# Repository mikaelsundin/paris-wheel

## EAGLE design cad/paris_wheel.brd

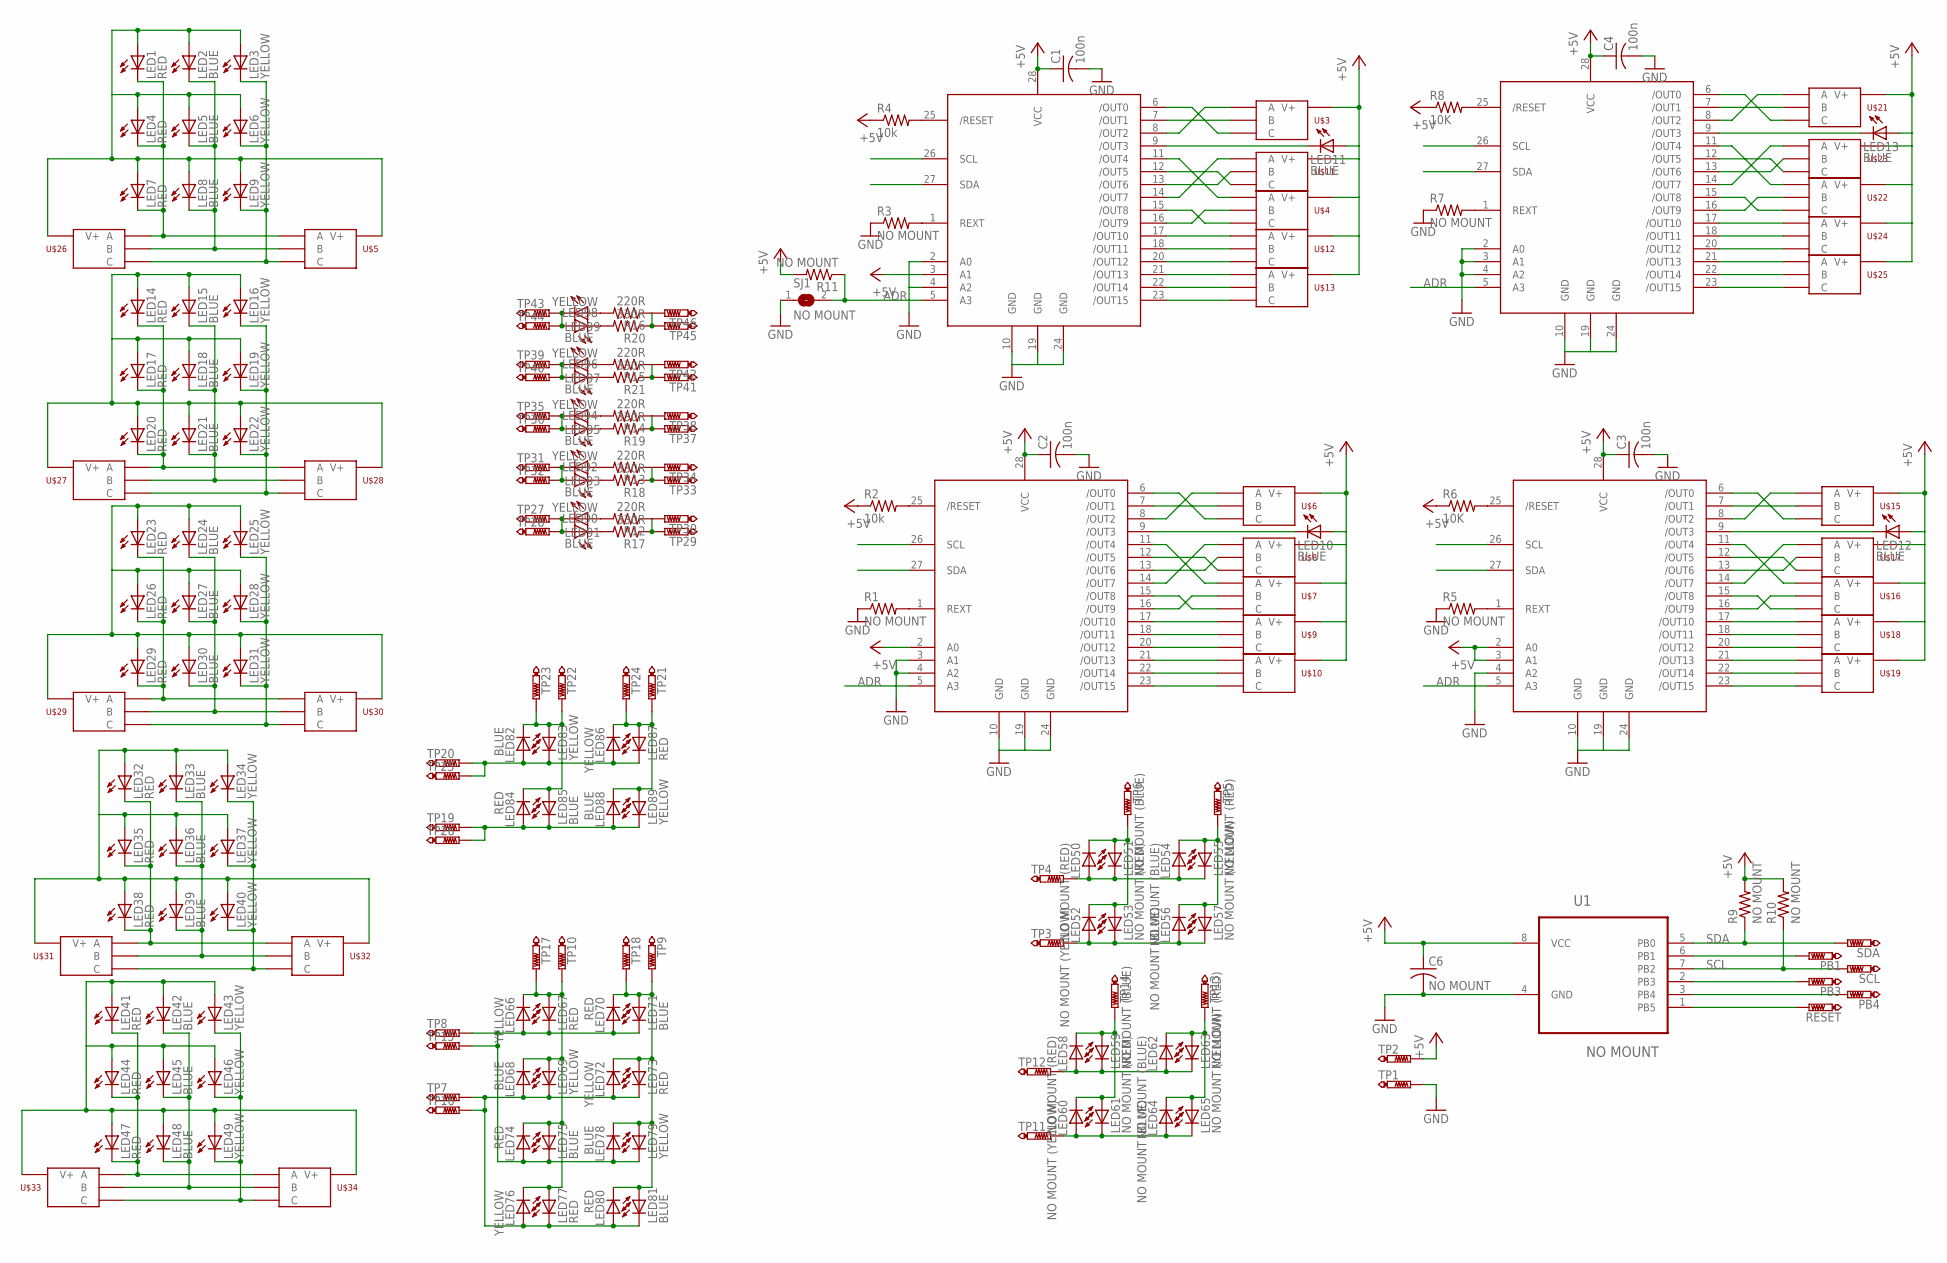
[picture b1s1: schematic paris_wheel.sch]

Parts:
C1, C2, C3, C4: 100n; C0603
C6: NO MOUNT; C0603
LED1, LED4, LED7, LED14, LED17, LED20, LED23, LED26, LED29, LED32, LED35, LED38, LED41, LED44, LED47, LED67, LED70, LED73, LED74, LED77, LED80, LED84, LED87: RED; CHIP-LED0603
LED2, LED5, LED8, LED10, LED11, LED12, LED13, LED15, LED18, LED21, LED24, LED27, LED30, LED33, LED36, LED39, LED42, LED45, LED48, LED68, LED71, LED75, LED78, LED81, LED82, LED85, LED88, LED91, LED93, LED95, LED97, LED99: BLUE; CHIP-LED0603
LED3, LED6, LED9, LED16, LED19, LED22, LED25, LED28, LED31, LED34, LED37, LED40, LED43, LED46, LED49, LED66, LED69, LED72, LED76, LED79, LED83, LED86, LED89, LED90, LED92, LED94, LED96, LED98: YELLOW; CHIP-LED0603
LED50, LED53, LED55, LED58, LED61, LED63: NO MOUNT (RED); CHIP-LED0603
LED51, LED54, LED56, LED59, LED62, LED64: NO MOUNT (BLUE); CHIP-LED0603
LED52, LED57, LED60, LED65: NO MOUNT (YELLOW); CHIP-LED0603
PB1, PB3, PB4: TESTPAD; TP20SQ
R1, R3, R5, R7, R9, R10, R11: NO MOUNT; R0603
R2, R4: 10k; R0603
R6, R8: 10K; R0603
R12, R13, R14, R15, R16: 220R; R0603
R17, R18, R19, R20, R21: 330R; R0603
RESET: TESTPAD; TP20SQ
SCL: TESTPAD; TP20SQ
SDA: TESTPAD; TP20SQ
SJ1: NO MOUNT; SJ
TP1, TP2: TESTPAD; TP20SQ
TP3, TP4, TP5, TP6, TP7, TP8, TP9, TP10, TP11, TP12, TP13, TP14, TP15, TP16, TP17, TP18, TP19, TP20, TP21, TP22, TP23, TP24, TP25, TP26, TP27, TP28, TP29, TP30, TP31, TP32, TP33, TP34, TP35, TP36, TP37, TP38, TP39, TP40, TP41, TP42, TP43, TP44, TP45, TP46: TESTPAD; TP15SQ
U1: NO MOUNT; SOIC127P798X216-8N
U$1, U$2, U$14, U$20: TLC59116IPWR; TSSOP28
U$3, U$4, U$5, U$6, U$7, U$8, U$9, U$10, U$11, U$12, U$13, U$15, U$16, U$17, U$18, U$19, U$21, U$22, U$23, U$24, U$25, U$26, U$27, U$28, U$29, U$30, U$31, U$32, U$33, U$34: NO MOUNT; MINI-PCB-CONNECTOR

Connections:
+5V: C1.1, C2.1, C3.1, C4.1, C6.1, LED10.A, LED11.A, LED12.A, LED13.A, R2.1, R4.1, R6.1, R8.1, R9.2, R10.2, R11.2, TP2.TP, U1.8 (VCC), U$1.2 (A0), U$1.28 (VCC), U$2.3 (A1), U$2.28 (VCC), U$3.A (V+), U$4.A (V+), U$6.A (V+), U$7.A (V+), U$8.A (V+), U$9.A (V+), U$10.A (V+), U$11.A (V+), U$12.A (V+), U$13.A (V+), U$14.2 (A0), U$14.3 (A1), U$14.28 (VCC), U$15.A (V+), U$16.A (V+), U$17.A (V+), U$18.A (V+), U$19.A (V+), U$20.28 (VCC), U$21.A (V+), U$22.A (V+), U$23.A (V+), U$24.A (V+), U$25.A (V+)
ADR: R11.1, SJ1.2, U$1.5 (A3), U$2.5 (A3), U$14.5 (A3), U$20.5 (A3)
GND: C1.2, C2.2, C3.2, C4.2, C6.2, R1.1, R3.1, R5.1, R7.1, SJ1.1, TP1.TP, U1.4 (GND), U$1.3 (A1), U$1.4 (A2), U$1.10 (GND), U$1.19 (GND), U$1.24 (GND), U$2.2 (A0), U$2.4 (A2), U$2.10 (GND), U$2.19 (GND), U$2.24 (GND), U$14.4 (A2), U$14.10 (GND), U$14.19 (GND), U$14.24 (GND), U$20.2 (A0), U$20.3 (A1), U$20.4 (A2), U$20.10 (GND), U$20.19 (GND), U$20.24 (GND)
unnamed: R2.2, U$1.25 (/RESET)
unnamed: LED1.A, LED2.A, LED3.A, LED4.A, LED5.A, LED6.A, LED7.A, LED8.A, LED9.A, U$5.A (V+), U$26.B (V+)
unnamed: R3.2, U$2.1 (REXT)
unnamed: LED1.C, LED4.C, LED7.C, U$5.V+ (A), U$26.C (A)
unnamed: LED2.C, LED5.C, LED8.C, U$5.C (B), U$26.V+ (B)
unnamed: LED3.C, LED6.C, LED9.C, U$5.B (C), U$26.A (C)
unnamed: U$1.6 (/OUT0), U$6.B (C)
unnamed: R1.2, U$1.1 (REXT)
unnamed: U$2.7 (/OUT1), U$3.C (B)
unnamed: U$1.7 (/OUT1), U$6.C (B)
unnamed: U$1.8 (/OUT2), U$6.V+ (A)
unnamed: U$1.12 (/OUT5), U$8.B (C)
unnamed: U$1.13 (/OUT6), U$8.C (B)
unnamed: U$1.15 (/OUT8), U$7.B (C)
unnamed: U$1.16 (/OUT9), U$7.C (B)
unnamed: U$1.14 (/OUT7), U$8.V+ (A)
unnamed: U$1.11 (/OUT4), U$7.V+ (A)
unnamed: U$1.17 (/OUT10), U$9.V+ (A)
unnamed: U$1.18 (/OUT11), U$9.C (B)
unnamed: U$1.20 (/OUT12), U$9.B (C)
unnamed: U$1.21 (/OUT13), U$10.V+ (A)
unnamed: U$1.22 (/OUT14), U$10.C (B)
unnamed: U$1.23 (/OUT15), U$10.B (C)
unnamed: LED10.C, U$1.9 (/OUT3)
unnamed: U$2.17 (/OUT10), U$12.V+ (A)
unnamed: U$2.18 (/OUT11), U$12.C (B)
unnamed: U$2.20 (/OUT12), U$12.B (C)
unnamed: U$2.21 (/OUT13), U$13.V+ (A)
unnamed: U$2.22 (/OUT14), U$13.C (B)
unnamed: U$2.23 (/OUT15), U$13.B (C)
unnamed: U$2.13 (/OUT6), U$11.C (B)
unnamed: U$2.11 (/OUT4), U$4.V+ (A)
unnamed: LED11.C, U$2.9 (/OUT3)
unnamed: U$2.6 (/OUT0), U$3.B (C)
unnamed: U$2.8 (/OUT2), U$3.V+ (A)
unnamed: U$2.15 (/OUT8), U$4.B (C)
unnamed: U$2.16 (/OUT9), U$4.C (B)
unnamed: U$2.12 (/OUT5), U$11.B (C)
unnamed: U$2.14 (/OUT7), U$11.V+ (A)
unnamed: R4.2, U$2.25 (/RESET)
unnamed: R5.2, U$14.1 (REXT)
unnamed: U$14.7 (/OUT1), U$15.C (B)
unnamed: U$14.17 (/OUT10), U$18.V+ (A)
unnamed: U$14.18 (/OUT11), U$18.C (B)
unnamed: U$14.20 (/OUT12), U$18.B (C)
unnamed: U$14.21 (/OUT13), U$19.V+ (A)
unnamed: U$14.22 (/OUT14), U$19.C (B)
unnamed: U$14.23 (/OUT15), U$19.B (C)
unnamed: U$14.13 (/OUT6), U$17.C (B)
unnamed: U$14.11 (/OUT4), U$16.V+ (A)
unnamed: LED12.C, U$14.9 (/OUT3)
unnamed: U$14.6 (/OUT0), U$15.B (C)
unnamed: U$14.8 (/OUT2), U$15.V+ (A)
unnamed: U$14.15 (/OUT8), U$16.B (C)
unnamed: U$14.16 (/OUT9), U$16.C (B)
unnamed: U$14.12 (/OUT5), U$17.B (C)
unnamed: U$14.14 (/OUT7), U$17.V+ (A)
unnamed: R6.2, U$14.25 (/RESET)
unnamed: R7.2, U$20.1 (REXT)
unnamed: U$20.7 (/OUT1), U$21.C (B)
unnamed: U$20.17 (/OUT10), U$24.V+ (A)
unnamed: U$20.18 (/OUT11), U$24.C (B)
unnamed: U$20.20 (/OUT12), U$24.B (C)
unnamed: U$20.21 (/OUT13), U$25.V+ (A)
unnamed: U$20.22 (/OUT14), U$25.C (B)
unnamed: U$20.23 (/OUT15), U$25.B (C)
unnamed: U$20.13 (/OUT6), U$23.C (B)
unnamed: U$20.11 (/OUT4), U$22.V+ (A)
unnamed: LED13.C, U$20.9 (/OUT3)
unnamed: U$20.6 (/OUT0), U$21.B (C)
unnamed: U$20.8 (/OUT2), U$21.V+ (A)
unnamed: U$20.15 (/OUT8), U$22.B (C)
unnamed: U$20.16 (/OUT9), U$22.C (B)
unnamed: U$20.12 (/OUT5), U$23.B (C)
unnamed: U$20.14 (/OUT7), U$23.V+ (A)
unnamed: R8.2, U$20.25 (/RESET)
unnamed: RESET.TP, U1.1 (PB5)
unnamed: PB3.TP, U1.2 (PB3)
unnamed: PB4.TP, U1.3 (PB4)
unnamed: PB1.TP, U1.6 (PB1)
unnamed: LED14.A, LED15.A, LED16.A, LED17.A, LED18.A, LED19.A, LED20.A, LED21.A, LED22.A, U$27.B (V+), U$28.A (V+)
unnamed: LED14.C, LED17.C, LED20.C, U$27.C (A), U$28.V+ (A)
unnamed: LED15.C, LED18.C, LED21.C, U$27.V+ (B), U$28.C (B)
unnamed: LED16.C, LED19.C, LED22.C, U$27.A (C), U$28.B (C)
unnamed: LED23.A, LED24.A, LED25.A, LED26.A, LED27.A, LED28.A, LED29.A, LED30.A, LED31.A, U$29.B (V+), U$30.A (V+)
unnamed: LED23.C, LED26.C, LED29.C, U$29.C (A), U$30.V+ (A)
unnamed: LED24.C, LED27.C, LED30.C, U$29.V+ (B), U$30.C (B)
unnamed: LED25.C, LED28.C, LED31.C, U$29.A (C), U$30.B (C)
unnamed: LED32.A, LED33.A, LED34.A, LED35.A, LED36.A, LED37.A, LED38.A, LED39.A, LED40.A, U$31.B (V+), U$32.A (V+)
unnamed: LED32.C, LED35.C, LED38.C, U$31.C (A), U$32.V+ (A)
unnamed: LED33.C, LED36.C, LED39.C, U$31.V+ (B), U$32.C (B)
unnamed: LED34.C, LED37.C, LED40.C, U$31.A (C), U$32.B (C)
unnamed: LED41.A, LED42.A, LED43.A, LED44.A, LED45.A, LED46.A, LED47.A, LED48.A, LED49.A, U$33.B (V+), U$34.A (V+)
unnamed: LED41.C, LED44.C, LED47.C, U$33.C (A), U$34.V+ (A)
unnamed: LED42.C, LED45.C, LED48.C, U$33.V+ (B), U$34.C (B)
unnamed: LED43.C, LED46.C, LED49.C, U$33.A (C), U$34.B (C)
unnamed: LED50.A, LED51.C, LED54.A, LED55.C, TP4.TP
unnamed: LED54.C, LED55.A, LED56.C, LED57.A, TP5.TP
unnamed: LED50.C, LED51.A, LED52.C, LED53.A, TP6.TP
unnamed: LED52.A, LED53.C, LED56.A, LED57.C, TP3.TP
unnamed: LED58.A, LED59.C, LED62.A, LED63.C, TP12.TP
unnamed: LED58.C, LED59.A, LED60.C, LED61.A, TP14.TP
unnamed: LED60.A, LED61.C, LED64.A, LED65.C, TP11.TP
unnamed: LED62.C, LED63.A, LED64.C, LED65.A, TP13.TP
unnamed: LED82.A, LED83.C, LED86.A, LED87.C, TP20.TP, TP25.TP
unnamed: LED82.C, LED83.A, LED84.C, LED85.A, TP22.TP, TP23.TP
unnamed: LED84.A, LED85.C, LED88.A, LED89.C, TP19.TP, TP26.TP
unnamed: LED86.C, LED87.A, LED88.C, LED89.A, TP21.TP, TP24.TP
unnamed: LED66.A, LED67.C, LED70.A, LED71.C, LED74.A, LED75.C, LED78.A, LED79.C, TP8.TP, TP15.TP
unnamed: LED66.C, LED67.A, LED68.C, LED69.A, LED74.C, LED75.A, LED76.C, LED77.A, TP10.TP, TP17.TP
unnamed: LED68.A, LED69.C, LED72.A, LED73.C, LED76.A, LED77.C, LED80.A, LED81.C, TP7.TP, TP16.TP
unnamed: LED70.C, LED71.A, LED72.C, LED73.A, LED78.C, LED79.A, LED80.C, LED81.A, TP9.TP, TP18.TP
unnamed: R12.1, R17.1, TP29.TP, TP30.TP
unnamed: LED90.A, LED91.C, TP27.TP, TP28.TP
unnamed: LED91.A, R12.2
unnamed: LED92.A, LED93.C, TP31.TP, TP32.TP
unnamed: R13.1, R18.1, TP33.TP, TP34.TP
unnamed: LED93.A, R13.2
unnamed: LED94.A, LED95.C, TP35.TP, TP36.TP
unnamed: R14.1, R19.1, TP37.TP, TP38.TP
unnamed: LED95.A, R14.2
unnamed: LED96.A, LED97.C, TP39.TP, TP40.TP
unnamed: R15.1, R21.1, TP41.TP, TP42.TP
unnamed: LED97.A, R15.2
unnamed: LED98.A, LED99.C, TP43.TP, TP44.TP
unnamed: R16.1, R20.1, TP45.TP, TP46.TP
unnamed: LED99.A, R16.2
unnamed: LED90.C, R17.2
unnamed: LED92.C, R18.2
unnamed: LED94.C, R19.2
unnamed: LED98.C, R20.2
unnamed: LED96.C, R21.2
SCL: R10.1, SCL.TP, U1.7 (PB2), U$1.26 (SCL), U$2.26 (SCL), U$14.26 (SCL), U$20.26 (SCL)
SDA: R9.1, SDA.TP, U1.5 (PB0), U$1.27 (SDA), U$2.27 (SDA), U$14.27 (SDA), U$20.27 (SDA)

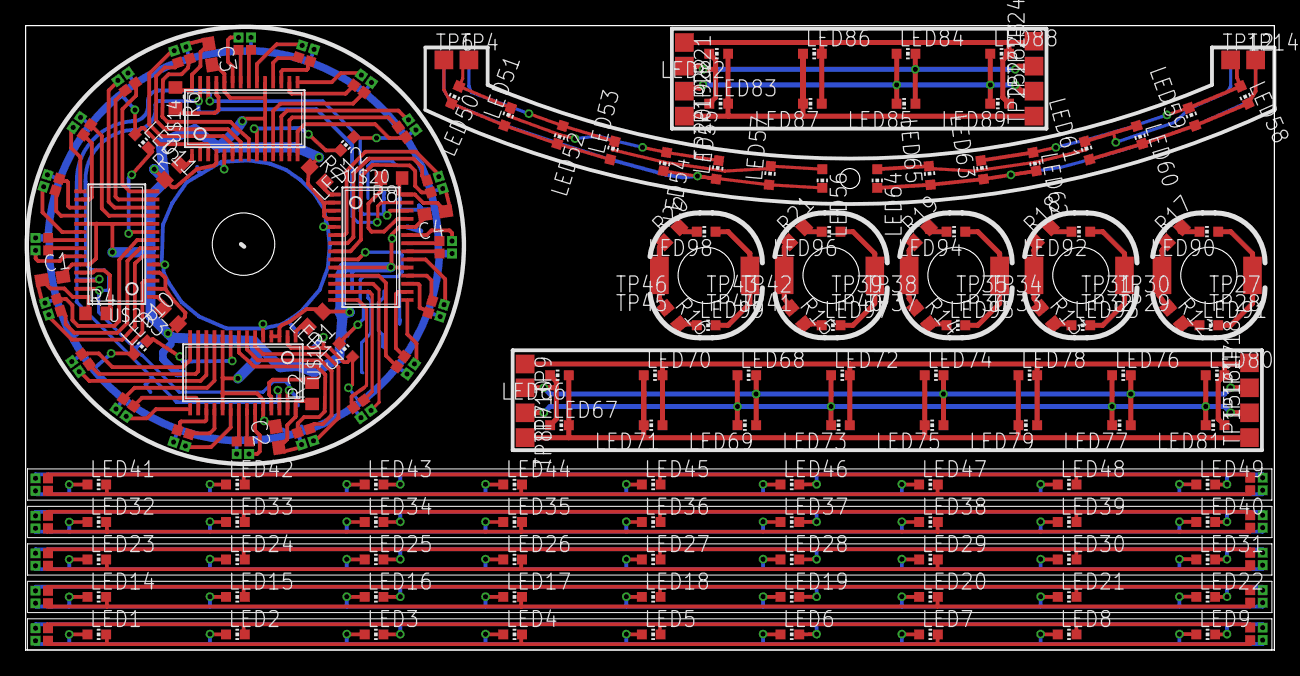
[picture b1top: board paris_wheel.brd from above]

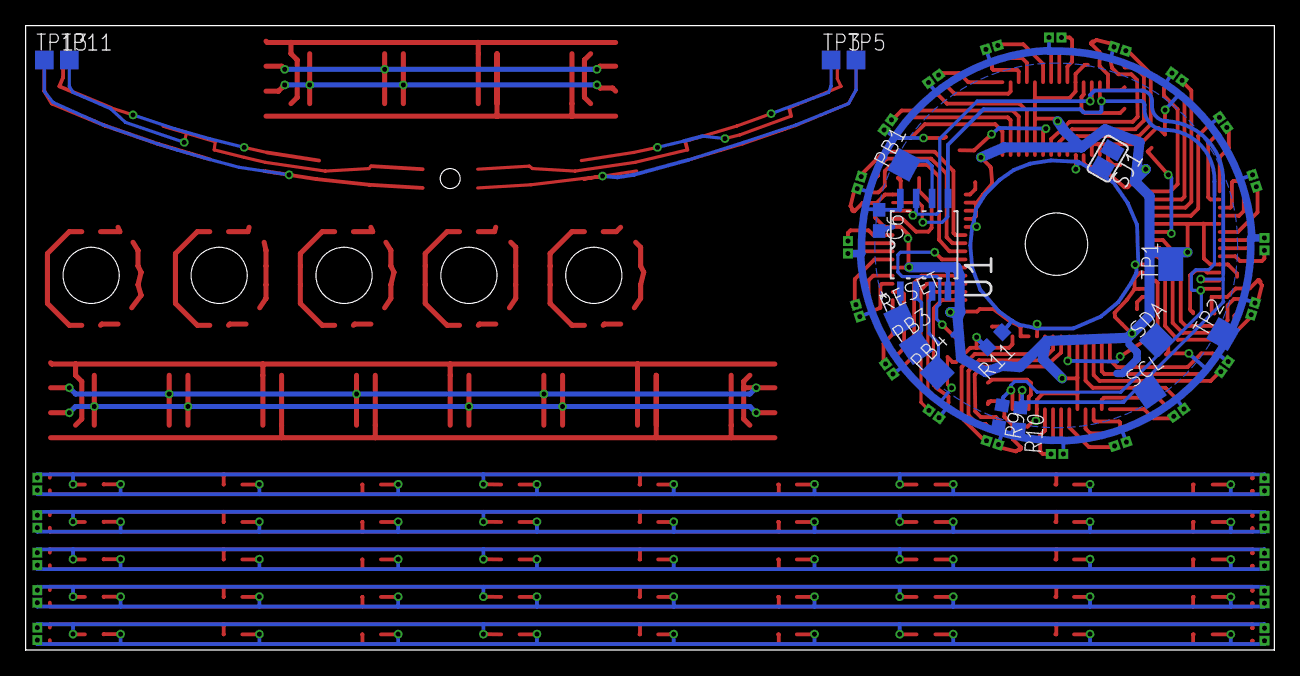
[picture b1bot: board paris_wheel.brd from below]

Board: 2 copper layers, 100.0 x 50.0 mm, 213 parts (18 on the bottom side), 137 nets.

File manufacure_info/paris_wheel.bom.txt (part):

Partlist exported from C:/Users/micke/Desktop/New folder (2)/paris_wheel.sch at 2015-07-17 01:03

Qty Value             Device                        Package            Parts                                                                                                                                                                                                                                                           Description                                             MPN           OC_FARNELL OC_NEWARK PACKAGE SUPPLIER TP_SIGNAL_NAME
4   100n              C-USC0603                     C0603              C1, C2, C3, C4                                                                                                                                                                                                                                                  CAPACITOR, American symbol                                                                                                
2   10K               R-US_R0603                    R0603              R6, R8                                                                                                                                                                                                                                                          RESISTOR, American symbol                                                                                                 
2   10k               R-US_R0603                    R0603              R2, R4                                                                                                                                                                                                                                                          RESISTOR, American symbol                                                                                                 
5   220R              R-US_R0603                    R0603              R12, R13, R14, R15, R16                                                                                                                                                                                                                                         RESISTOR, American symbol                                                                                                 
5   330R              R-US_R0603                    R0603              R17, R18, R19, R20, R21                                                                                                                                                                                                                                         RESISTOR, American symbol                                                                                                 
32  BLUE              LEDCHIP-LED0603               CHIP-LED0603       LED2, LED5, LED8, LED10, LED11, LED12, LED13, LED15, LED18, LED21, LED24, LED27, LED30, LED33, LED36, LED39, LED42, LED45, LED48, LED68, LED71, LED75, LED78, LED81, LED82, LED85, LED88, LED91, LED93, LED95, LED97, LED99                                     LED                                                                                                                       
1   NO MOUNT          ATTINY85-20SU                 SOIC127P798X216-8N U1                                                                                                                                                                                                                                                              8-bit Microcontroller with In-System Programmable Flash ATTINY85-20SU 1455164    58M3797   SOIC-8  Atmel                  
1   NO MOUNT          C-USC0603                     C0603              C6                                                                                                                                                                                                                                                              CAPACITOR, American symbol                                                                                                
25  NO MOUNT          MINI-PCB-CONNECTOR-DRIVE-SIDE MINI-PCB-CONNECTOR U$3, U$4, U$5, U$6, U$7, U$8, U$9, U$10, U$11, U$12, U$13, U$15, U$16, U$17, U$18, U$19, U$21, U$22, U$23, U$24, U$25, U$28, U$30, U$32, U$34                                                                                                                                                                                                                                             
5   NO MOUNT          MINI-PCB-CONNECTOR-LED-SIDE   MINI-PCB-CONNECTOR U$26, U$27, U$29, U$31, U$33                                                                                                                                                                                                                                                                                                                                                              
7   NO MOUNT          R-US_R0603                    R0603              R1, R3, R5, R7, R9, R10, R11                                                                                                                                                                                                                                    RESISTOR, American symbol                                                                                                 
1   NO MOUNT          SJ                            SJ                 SJ1                                                                                                                                                                                                                                                             SMD solder JUMPER                                                                                                         
6   NO MOUNT (BLUE)   LEDCHIP-LED0603               CHIP-LED0603       LED51, LED54, LED56, LED59, LED62, LED64                                                                                                                                                                                                                        LED                                                                                                                       
6   NO MOUNT (RED)    LEDCHIP-LED0603               CHIP-LED0603       LED50, LED53, LED55, LED58, LED61, LED63                                                                                                                                                                                                                        LED                                                                                                                       
4   NO MOUNT (YELLOW) LEDCHIP-LED0603               CHIP-LED0603       LED52, LED57, LED60, LED65                                                                                                                                                                                                                                      LED                                                                                                                       
23  RED               LEDCHIP-LED0603               CHIP-LED0603       LED1, LED4, LED7, LED14, LED17, LED20, LED23, LED26, LED29, LED32, LED35, LED38, LED41, LED44, LED47, LED67, LED70, LED73, LED74, LED77, LED80, LED84, LED87                                                                                                    LED                                                                                                                       
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
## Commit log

2015-07-22 Initial commit. both manufacture info and cad exist.
